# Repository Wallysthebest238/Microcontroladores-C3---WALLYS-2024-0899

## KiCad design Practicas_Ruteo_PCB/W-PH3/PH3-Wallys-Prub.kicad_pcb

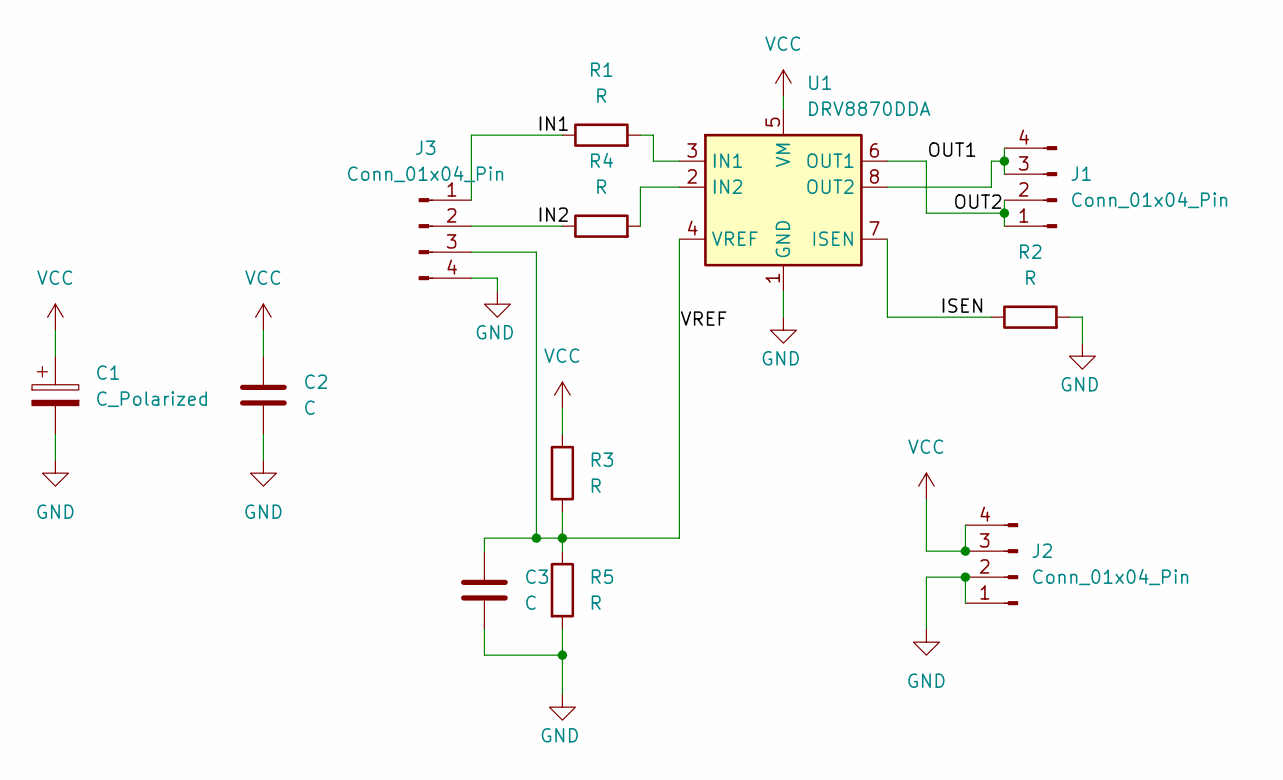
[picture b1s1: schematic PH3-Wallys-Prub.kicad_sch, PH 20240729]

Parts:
C1: C_Polarized; CP_Elec_8x10.5
C2, C3: C; R_0805_2012Metric
J1, J2, J3: Conn_01x04_Pin; Conector castellado
R1, R3, R4, R5: R; R_0805_2012Metric
R2: R; C_1206_3216Metric
U1: DRV8870DDA; Texas_HTSOP-8-1EP_3.9x4.9mm_P1.27mm_EP2.95x4.9mm_Mask2.4x3.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

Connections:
/IN1: J3.1, R1.1
/IN2: J3.2, R4.1
/ISEN: R2.1, U1.7 (ISEN)
/OUT1: J1.1, J1.2, U1.6 (OUT1)
/VREF: C3.1, J3.3, R3.2, R5.1, U1.4 (VREF)
GND: C1.2, C2.2, C3.2, J2.1, J2.2, J3.4, R2.2, R5.2, U1.1 (GND), U1.9 (GND)
unnamed: J1.3, J1.4, U1.8 (OUT2)
unnamed: R1.2, U1.3 (IN1)
unnamed: R4.2, U1.2 (IN2)
VCC: C1.1, C2.1, J2.3, J2.4, R3.1, U1.5 (VM)

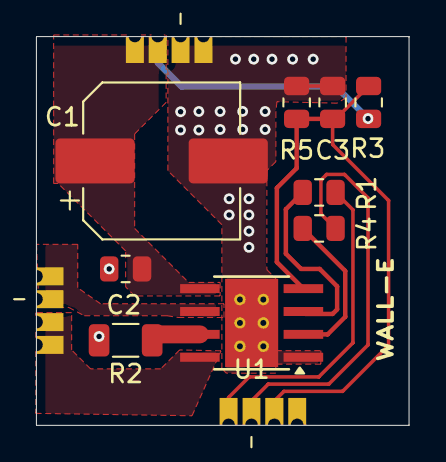
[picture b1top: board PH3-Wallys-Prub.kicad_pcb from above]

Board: 2 copper layers, 20.7 x 21.6 mm, 12 parts (0 on the bottom side), 10 nets.

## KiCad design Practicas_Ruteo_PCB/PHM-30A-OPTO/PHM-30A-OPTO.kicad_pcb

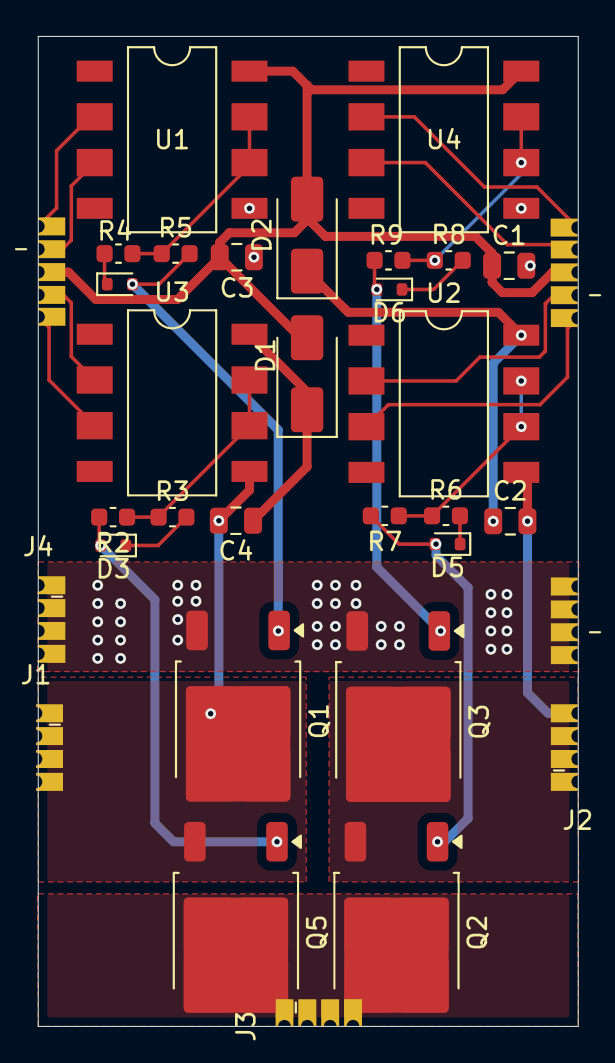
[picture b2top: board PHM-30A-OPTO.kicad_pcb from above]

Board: 2 copper layers, 30.0 x 55.0 mm, 33 parts (0 on the bottom side), 27 nets.

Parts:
C1, C2, C3, C4: C; C_0805_2012Metric
D1, D2: US1A; D_SMA
D3, D4, D5, D6: 1N4148WT; D_SOD-523
J1, J2, J3, J4: Conn_01x04_Socket; PinSocket_1x04_P1.27mm_Castellated
J5, J7: Conn_01x05_Socket; Conector castellado_5pines
J6: Conn_01x04_Socket; Conector castellado
Q1, Q2, Q3, Q5: QM6006D; TO-252-2
R2, R3, R4, R5, R6, R7, R8, R9: R_US; C_0603_1608Metric
U1, U2, U3, U4: HCPL-3120; PowerIntegrations_SMD-8

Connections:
/Lado A: C4.2, J1.1, J1.2, J1.3, J1.4, Q1.2 (D), Q5.3 (S), U3.5 (VEE)
/Lado B: C2.2, J2.1, J2.2, J2.3, J2.4, Q2.3 (S), Q3.2 (D), U2.5 (VEE)
GND: C1.2, C3.2, J4.1, J4.2, J4.3, J4.4, J6.1, J6.2, J6.3, J6.4, Q1.3 (S), Q3.3 (S), U1.5 (VEE), U4.5 (VEE)
unnamed: C4.1, D1.1 (K), U3.8 (VCC)
unnamed: C2.1, D2.1 (K), U2.8 (VCC)
unnamed: D3.2 (A), Q5.1 (G), R2.2
unnamed: D3.1 (K), R3.2
unnamed: D4.2 (A), Q1.1 (G), R5.2
unnamed: D4.1 (K), R4.2
unnamed: D5.2 (A), Q2.1 (G), R7.2
unnamed: D5.1 (K), R6.2
unnamed: D6.2 (A), Q3.1 (G), R9.2
unnamed: D6.1 (K), R8.2
unnamed: J5.1, U2.3 (C)
unnamed: J5.2, U2.2 (A)
unnamed: J5.4, U4.3 (C)
unnamed: J5.5, U4.2 (A)
unnamed: J7.1, U1.2 (A)
unnamed: J7.2, U1.3 (C)
unnamed: J7.4, U3.2 (A)
unnamed: J7.5, U3.3 (C)
unnamed: R2.1, R3.1, U3.6 (VO), U3.7 (VO)
unnamed: R4.1, R5.1, U1.6 (VO), U1.7 (VO)
unnamed: R6.1, R7.1, U2.6 (VO), U2.7 (VO)
unnamed: R8.1, R9.1, U4.6 (VO), U4.7 (VO)
VBUS: J3.1, J3.2, J3.3, J3.4, Q2.2 (D), Q5.2 (D)
VCC: C1.1, C3.1, D1.2 (A), D2.2 (A), J5.3, J7.3, U1.8 (VCC), U4.8 (VCC)

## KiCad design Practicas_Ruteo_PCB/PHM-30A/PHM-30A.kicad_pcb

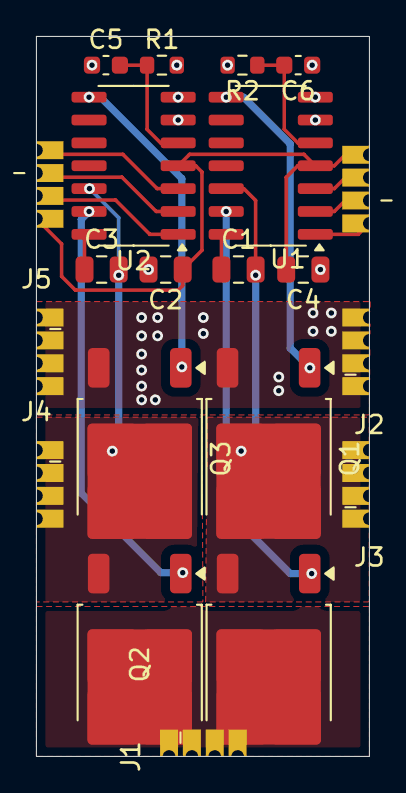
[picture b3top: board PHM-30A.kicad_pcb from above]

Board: 2 copper layers, 18.5 x 40.0 mm, 21 parts (0 on the bottom side), 19 nets.

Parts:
C1, C2, C3, C4: C; C_0805_2012Metric
C5, C6: C; C_0603_1608Metric
J1, J2, J3, J4, J5: Conn_01x04_Socket; PinSocket_1x04_P1.27mm_Castellated
J6, J7: Conn_01x04_Socket; Conector castellado
Q1, Q2, Q3, Q5: QM6006D; TO-252-2
R1, R2: R_US; R_0603_1608Metric
U1, U2: L6491; SO-14_3.9x8.65mm_P1.27mm

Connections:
/A: C1.2, J3.1, J3.2, J3.3, J3.4, Q1.2 (D), Q5.3 (S), U1.12 (OUT)
/B: C3.2, J4.1, J4.2, J4.3, J4.4, Q2.3 (S), Q3.2 (D), U2.12 (OUT)
/HIN_D: J7.1, U2.3 (HIN)
/HIN_I: J6.3, U1.3 (HIN)
/LIN_D: J7.3, U2.1 (~LIN)
/LIN_I: J6.1, U1.1 (~LIN)
/SD_D: J7.2, U2.2 (~SD/OD)
/SD_I: J6.2, U1.2 (~SD/OD)
/VH: J1.1, J1.2, J1.3, J1.4, Q2.2 (D), Q5.2 (D)
GND: C2.2, C4.1, C5.1, C6.1, J2.1, J2.2, J2.3, J2.4, J5.1, J5.2, J5.3, J5.4, Q1.3 (S), Q3.3 (S), R1.2, R2.2, U1.6 (SGND), U1.7 (PGND), U2.6 (SGND), U2.7 (PGND)
unnamed: Q1.1 (G), U1.8 (LVG)
unnamed: Q2.1 (G), U2.13 (HVG)
unnamed: Q3.1 (G), U2.8 (LVG)
unnamed: Q5.1 (G), U1.13 (HVG)
unnamed: C1.1, U1.14 (BOOT)
unnamed: C6.2, R2.1, U1.5 (DT)
unnamed: C3.1, U2.14 (BOOT)
unnamed: C5.2, R1.1, U2.5 (DT)
VCC: C2.1, C4.2, J6.4, J7.4, U1.4 (VCC), U2.4 (VCC)

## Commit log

2025-09-11 Primer guardado jevi
2025-10-08 Este es el guardo de las tareas aun fala el Puerton
2025-10-09 Guardado general 07/10/2025
2025-10-09 Guardado completo
2025-10-09 Listo
2025-10-30 Guardado del proyecto puerton App
2025-11-12 actualizacion (guardado del 8/11/2025)
2025-12-02 Practicas Ready
